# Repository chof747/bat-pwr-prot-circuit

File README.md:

# Battery Protection Circuit

Taken from  Great Scott's Design only the protection part + added simple down-regulation of voltage for 3v3 circuits.

The circuit is intended to work with the following circuit:
https://github.com/chof747/battery-holder-hardware

It contains the following elements:

 - FS312F-G LiIon protection circut
 - Mosfets to trigger the charging and discharging
 - A ME6211C33M5G 3v3 low dropout voltage regulator
 - Pinouts for to be placed on a breadboard as power supply
 - Pinouts to connect the charging circuit and the battery

## Todo

Requires confirmation if this setup is working

## Revision History:

 - **v1.0**: Initial Version (filed for fabrication: 04.12.2022, successfully assembled 15.02.2023)
 - **v1.1**: First revision with seperated Bat+ and 3v3 line (filed for fabrication 19.04.2023)

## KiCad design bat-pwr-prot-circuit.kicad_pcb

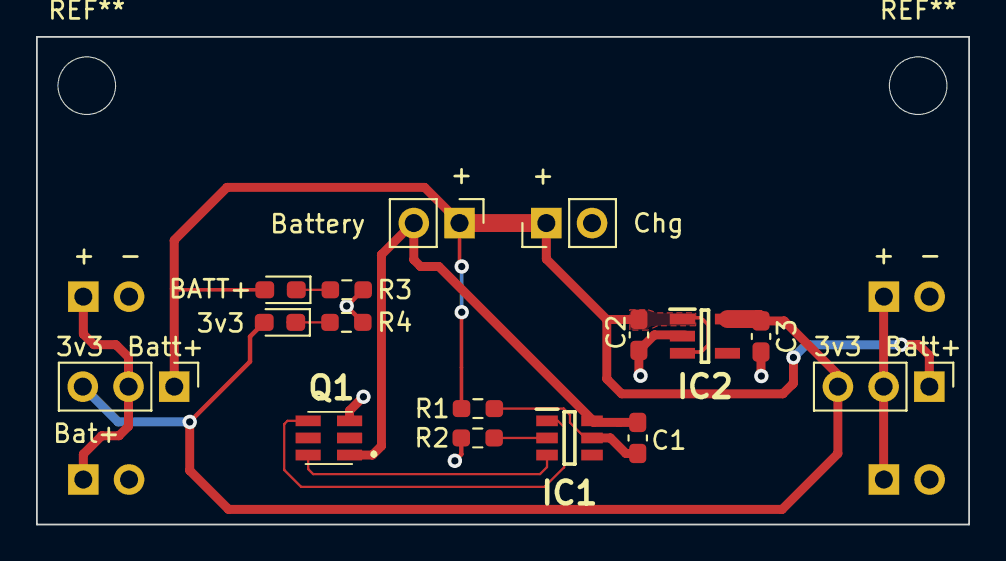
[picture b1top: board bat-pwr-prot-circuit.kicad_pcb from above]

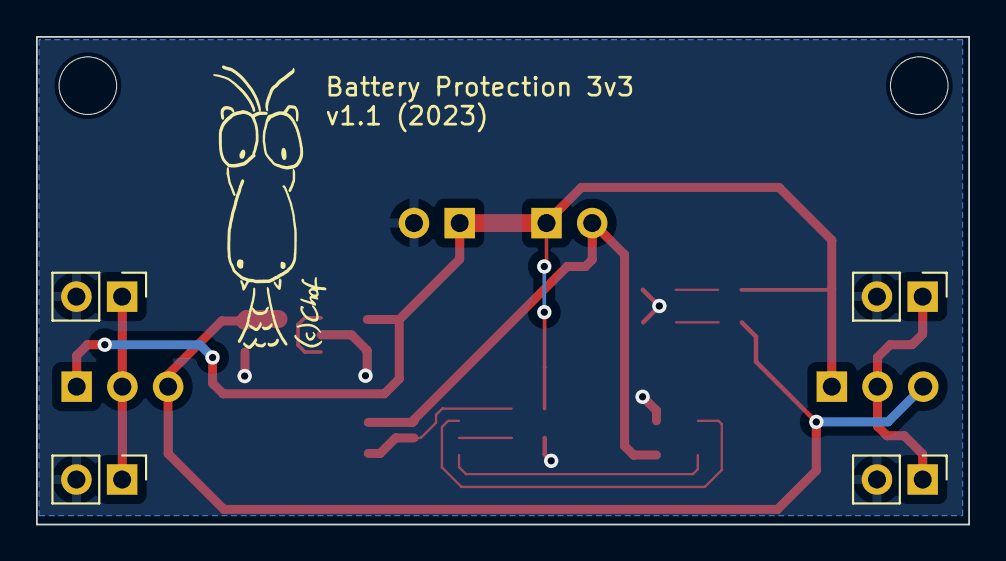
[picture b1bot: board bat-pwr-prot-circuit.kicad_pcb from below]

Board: 2 copper layers, 51.8 x 27.1 mm, 20 parts (4 on the bottom side), 12 nets.

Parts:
C1: 0.1uF; C_0603_1608Metric_Pad1.08x0.95mm_HandSolder
C2, C3: 1uF; C_0603_1608Metric_Pad1.08x0.95mm_HandSolder
D1: BATT+; LED_0603_1608Metric_Pad1.05x0.95mm_HandSolder
D2: 3v3; LED_0603_1608Metric_Pad1.05x0.95mm_HandSolder
IC1: FS312F-G; SOT95P280X145-6N
IC2: 3v3 Regulator; SOT95P270X145-5N
J1, J4: Bat+; PinHeader_1x02_P2.54mm_Vertical
J2, J5: 3v3; PinHeader_1x02_P2.54mm_Vertical
J3: Battery; PinHeader_1x02_P2.54mm_Vertical
J6: Chg; PinHeader_1x02_P2.54mm_Vertical
JL1: Conn_01x03; PinHeader_1x03_P2.54mm_Vertical
JR1: Conn_01x03; PinHeader_1x03_P2.54mm_Vertical
Q1: FS8205
R1: 100; R_0603_1608Metric_Pad0.98x0.95mm_HandSolder
R2: 2k; R_0603_1608Metric_Pad0.98x0.95mm_HandSolder
R3, R4: 680; R_0603_1608Metric_Pad0.98x0.95mm_HandSolder

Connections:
+3V3: C3.1, D2.2 (A), IC2.5 (VOUT), JL1.3, JR1.3
/BATT+: C2.1, D1.2 (A), IC2.1 (VIN), IC2.3 (CE), J3.1, J6.1, JL1.1, JR1.1, R1.2
/BATT-: C1.2, IC1.6 (GND), J3.2, Q1.1 (S1)
/Left: J1.1, J4.1, JL1.2
/Right: J2.1, J5.1, JR1.2
/VCC: C1.1, IC1.5 (VCC), R1.1
GND: C2.2, C3.2, IC2.2 (VSS), J1.2, J2.2, J4.2, J5.2, J6.2, Q1.3 (S2), R2.2, R3.2, R4.2
unnamed: D1.1 (K), R3.1
unnamed: D2.1 (K), R4.1
unnamed: IC1.1 (OD), Q1.6 (G1)
unnamed: IC1.2 (CS), R2.1
unnamed: IC1.3 (OC), Q1.4 (G2)

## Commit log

2022-12-04 Revision one - with double mosfet
2022-12-04 Updated README after ordering
2023-02-16 Selectable rails and led indicators
    - Added pin selectory to configure the left and right rail connectors individually for batt+ and 3v3
    - Added led indicators for batt+ and 3v3
2023-04-20 Adapted .gitignore to newest version
2023-04-20 Revision 1.1 commit
    - Separated power lines to Bat+ and 3v3
    - Added selector pins for each side of the board
    - Added mounting holes
    - Improved the labeling on the front
    - Added logo
2023-04-27 Updated template for KiCAD 7
2023-09-30 modified .gitignore to leave out bom html
2024-07-18 Updated footprints to kicad8
